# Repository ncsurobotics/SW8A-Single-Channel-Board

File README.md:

# SW8A-Single_Channles-Board Rev_1.0
This is for the development of the Acoustics PCB as single channels

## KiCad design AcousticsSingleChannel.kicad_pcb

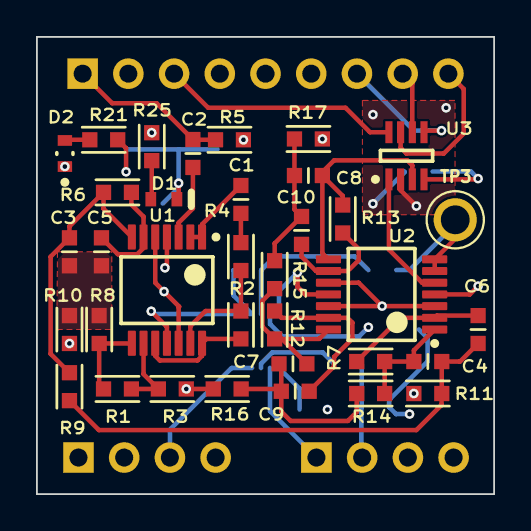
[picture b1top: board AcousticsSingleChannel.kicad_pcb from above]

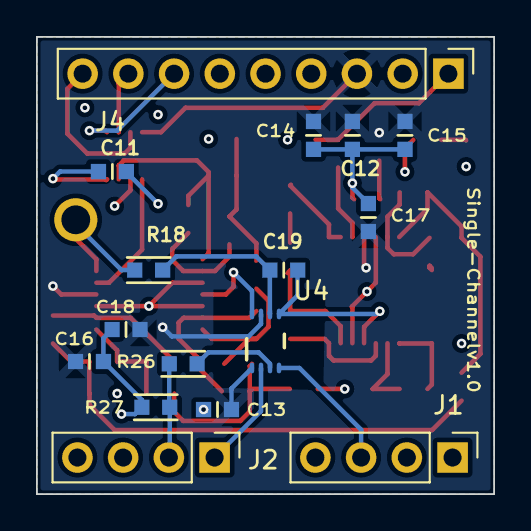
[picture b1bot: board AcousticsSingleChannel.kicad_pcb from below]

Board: 4 copper layers, 25.4 x 25.4 mm, 51 parts (16 on the bottom side), 36 nets.

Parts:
C1, C2: 5100pF; SMD-0603C
C3, C4, C5, C6, C7, C8, C9, C10: 1000pF; SMD-0603C
C11, C13, C14, C15, C16, C17, C18: 1µF; SMD-0603C
C12: 0.10µF; SMD-0603C
C19: 1.5nF; SMD-0603C
D1: TLMS1100-GS08; VISH-TLMX1100_V
D2: TLMP1100-GS08; FP-6_541-5056_01-4-MFG
J1, J2: Conn_01x04_Pin; PinHeader_1x04_P2.54mm_Vertical
J4: Conn_01x09_Pin; PinHeader_1x09_P2.54mm_Vertical
R1, R2, R4: 10k; SMD-0603-RES
R3: 1k; SMD-0603-RES
R5: 4.7k; SMD-0603-RES
R6: 54.9k; SMD-0603-RES
R7: 41.2k; SMD-0603-RES
R8: 17.4k; SMD-0603-RES
R9: 13k; SMD-0603-RES
R10: 698; SMD-0603-RES
R11: 536; SMD-0603-RES
R12: 165k; SMD-0603-RES
R13: 86.6k; SMD-0603-RES
R14: 11k; SMD-0603-RES
R15: 5.76k; SMD-0603-RES
R16: 332; SMD-0603-RES
R17: 174; SMD-0603-RES
R18: 25; SMD-0603-RES
R21, R25: 300; SMD-0603-RES
R26, R27: 0; SMD-0603-RES
TP3: 5005; KEYSTONE_5005
U1, U2: OPA1604AIPWR; PW0014A_N
U3: LTC6910-3CTS8#TRPBF; LT-TS8-8-TSOT-23_V
U4: ADS7042IDCUR; DCU0008A_L

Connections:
+3.3V: C12.2, C13.1, C14.2, C15.2, C16.2, C17.2, C18.1, J4.3, R25.2, U1.4 (V+), U2.4 (V+), U3.8 (V+), U4.1 (DVDD), U4.7 (AVDD)
/Band Pass Filter/BPF_OUT: C8.2, R13.2, U2.8 (OUT_C), U3.3 (IN)
/Band Pass Filter/F1_In: C3.1, C5.1, R8.2, R10.2
/Band Pass Filter/F1_Out: C3.2, R6.2, R9.1, U1.7 (OUT_B)
/Band Pass Filter/F2_In: C4.1, C6.1, R9.2, R11.2
/Band Pass Filter/F2_Out: C4.2, R7.2, R14.1, U2.1 (OUT_A)
/Band Pass Filter/F3_In: C7.1, C9.1, R14.2, R16.2
/Band Pass Filter/F3_Out: C7.2, R12.2, R15.1, U2.14 (OUT_D)
/Band Pass Filter/F4_In: C8.1, C10.1, R15.2, R17.2
/BufferBiasAmp/BBA_OUT: R1.2, R8.1, U1.8 (OUT_C)
/BufferBiasAmp/BBAmp_IN: R2.2, U1.10 (IN_C+), U1.14 (OUT_D)
/BufferBiasAmp/BIAS_IN: C1.1, R4.1
/BufferBiasAmp/BUF_IN: C2.2, U1.3 (IN_A+)
/BufferBiasAmp/BUF_OUT: C1.2, U1.1 (OUT_A), U1.2 (IN_A-)
/CS: J1.3, U4.4 (CS_N)
/DOUT: R26.2, U4.3 (SDO)
/G0_out: J4.7, U3.5 (G0)
/G1_out: J4.8, U3.6 (G1)
/G2_out: J4.9, U3.7 (G2)
/Hydro+: C2.1, J4.1, R5.1
/Mode_Sel_3.3: J1.1, R5.2, R21.2
/OutputAmplifier/Amp_Out: U2.5 (IN_B+), U3.1 (OUT)
/SCLK: J2.1, U4.2 (SCLK)
/Sig_Out: R18.1, TP3.TP, U2.6 (IN_B-), U2.7 (OUT_B)
AGND: C11.1, J4.2, R3.1, R10.1, R11.1, R16.1, R17.1, U1.5 (IN_B+), U1.12 (IN_D+), U2.3 (IN_A+), U2.10 (IN_C+), U2.12 (IN_D+), U3.2 (AGND)
GND: C11.2, C12.1, C13.2, C14.1, C15.1, C16.1, C17.1, C18.2, C19.2, D1.2 (K), D2.1 (C), J4.5, R27.1, U1.11 (V-), U2.11 (V-), U3.4 (V-), U4.5 (AINM), U4.8 (GND)
unnamed: D1.1 (A), R25.1
unnamed: D2.2 (A), R21.1
unnamed: J2.2, R26.1, R27.2
unnamed: C5.2, R6.1, U1.6 (IN_B-)
unnamed: R1.1, R3.2, U1.9 (IN_C-)
unnamed: R2.1, R4.2, U1.13 (IN_D-)
unnamed: C6.2, R7.1, U2.2 (IN_A-)
unnamed: C10.2, R13.1, U2.9 (IN_C-)
unnamed: C9.2, R12.1, U2.13 (IN_D-)
unnamed: C19.1, R18.2, U4.6 (AINP)

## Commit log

2022-03-23 add gitignore and altium file folder
2022-03-23 Add acoustics folder in here
2022-03-28 All the single channel board work
2022-05-17 Added "0" ohm resistor to TLE2426, Added LTC690 & SW, Routed board
2022-05-18 Added bypasses, recreated polygon pour planes, routing adjustments
2022-05-21 Routing edits to conform to best practices from Marcus and Justin
2022-05-21 PCB review changes without Daniel's Amp circuit(U3) recommendations
2022-05-21 removed U1 and U2 from mechanical layers and added a board outline
2022-05-21 Didn't save project structure fully for last commit
2022-05-21 First branch commit
2022-05-21 Messy fix for Daniel's U-Amp (U3) findings in the datasheet
2022-05-22 First seven OP AMPs routed in an extremely condensed fashion. May need to spread out the components for ease of soldering.
2022-05-22 Cleaned up the schematics
2022-05-22 All connections made. Need to update LED resistor, find 9V header, spread out components, maybe reduce board size
2022-05-22 Spreadout under chip vias
2022-05-23 Net Labels added and components spread out
2022-05-24 Silk screen changes and additions
2022-05-24 silk screen shanges
2022-05-24 Added Silk Screens and a few net names
2022-05-25 Unsure maybe some silkscreen changes
2022-05-26 Added official header footprints
2022-05-26 Messing with Libraries Library
2022-05-26 Using manufacturer parts
2022-05-27 Added mounting hole
2022-05-27 State of project for PCB order
2022-05-29 Reorganized file structure
2022-05-29 cleaned local directory resulting in some changes to .PrjPCB
2022-09-20 Added annotations and removed unnnecessary parts
2023-01-10 Added outjob files. Updated Routing.
2023-01-17 added the voltage divider resistors
2023-01-17 Fix trace position to match clearance requirements
2023-01-17 Fix silkscreen branding
2023-03-07 made additions for board labeling and change headers and add probe points
2023-03-09 Added net labels
2023-03-30 moved probe via off of trace
2023-03-30 move silscreen for AMP probe
2023-04-04 Fix lots of design rule errors
2023-04-04 Edit to the location of J8 on the PCB. DRC threw silk screen clearance error. Solved, polygons re-poured. 0 Violation in DRC.
2023-04-04 added hydrophone on indicator LED
2023-04-04 Add logos
2023-04-11 Converted Altium to Kicad
2023-06-05 Add license
2023-07-04 Fix gitignore
2023-07-04 Remove remaining altium files
2023-07-04 Fix various net and footprint issues
2023-07-04 Fix logos
2023-07-04 Cleanup symbol table
2023-10-24 Update fixing local weirdness? Changed some trace widths
2023-10-24 Fixed routing
2023-11-07 Hopefully it works this time
2024-01-18 deleted lock file
2024-01-18 Fixed small issue with trace width
2026-02-08 Ready for review
2026-02-09 Ready for Review.
2026-02-20 Changed headers.
2026-02-26 spacing
2026-02-26 tracks
2026-02-27 Changed pinouts causing minor changes to layer1 layout.
2026-02-27 changed pinouts, causing major changes to layout mostly on layer1.
2026-02-28 Layer Stackup Updates.
